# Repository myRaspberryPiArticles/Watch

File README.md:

# Watch
An analog IC chip watch powered with a LiPo and outputs in digital time on segment displays! Analog, or digital!? Thanks to Hackclub Forge and PCBWay for making this possible! Go check them out and make cool things like this as well! Here is more about it!:

## Pictures - _a picture tells 1000 words_
<p align="center">

</p>

## What does is it do? 
This watch is my V1 of a fully analog circuit, and by far the most complex PCB I have made. The aim is for it to be able to keep track of time precisely and then output it to four 7-segment displays, for the user to see when they have clicked the show time button. Usually, a watch would show the time constantly, but because  of battery constraints, I had to adapt to make it only show when the user wanted it to be seen. The 7-segment displays automatically wrap around after hitting 23:59, as it is the 24 hour clock's largest possible time. All the details will be explained in the 'How does it work' section.

## Why did I build it?
This specific project has a far fetched origin story, but the gist is that I wanted to do something with a 555 Timer after seeing a normal wristwatch, then comparing it with my smart watch, then thinking what is in the middle of the two - whether the thing I should make should be analog, or digital. 

After reasoning around with Gemini for a bit, I realised I would unfortunately have to use something closer to an oscillator rather than a 555 Timer as I hoped. In this chat, I also figured out how some of the other stuff would work, which brings us to our next section for those interested.

## How does it work? - _@techy people, this is for you_
The question we are all wondering. There is such a complex PCB and schematic we have seen in the photos, and now we at least know what it is - but how does it work? The simple answer can be broken into some few blocks and sections of the hardware, that eventually make the watch work. The blocks go as such:

1. Timer block (SG-3030CM gives a 32.768kHz pulse, then a 2^14 divider gets it down to 2Hz, then another divider to 1Hz) ---> 

2. Second to minute pulse block (two carry counter ICs that make the pulse 1/16Hz to input over to the display) ---> 

3. Display block (CD4026s that output to super small 0.2" segment displays) ---> 

4. And-gate wrap around (74HC08 IC that supplies quad 2 input and-gates for detecting certain segments)

## PCB and layout - _There is no greater optimism than ordering 500 boards without testing the prototype first._
As seen in the picture, the PCB is quite busy, with their being 701 trace segments, 258 pads, 73 vias, and a total of 123 nets. All these components have to fit in a wristwatch size of 35x42mm, and there are over 30 resistors and capacitors. To fit them all with enough space for a copper zone to pour, and to fit traces, I had to move over some parts to the back, but this means I will have to get a more advanced way of manufacturing it.

The way I was able to do this, with not much KiCAD experience was by logically splitting up the components, and wiring them one by one. this means I first made a display block with all the appropriate IC chips and resistors. After wiring them as needed, I then moved the m to a central position in the board to ensure there was enough space for the other components. then I fit in thew other timer units around where they could be inserted, before tracing them as well and then adding zones. I have two zones, on the back and front, for power and ground, and this meant I had to use many vias. To remove some random, useless copper zone islands, I had to use the 'do not fill' tool.

If you want a more chronological timeline of how I built this, check out my JOURNAL.md above!

## BOM - _NOT A BOMB!_
| Part | Where to buy | Cost |
| :--- | :---: | ---: |
| Segment Displays | [Ebay](https://www.ebay.co.uk/itm/195889276369?_skw=0.2%22+segment+display&itmmeta=01M6EP70M7ABXRD5BKFYGM1NHH&hash=item2d9be925d1%3Ag%3ATBIAAOSw2qplWLlX&itmprp=enc%3AAQALAAAA0CHNgUiiE%2FjQhlDTaMiAde8N4pqQcRs8IX6DydODM23mOmGth8nYc7n8xlrxr%2BS6NNEPMCjCPPxBPjypG0T%2B5PGzBhXTQX7kgbtBIbUk7yeaSZlJJ6amFuhsQ36oQ9b2yuffzb50OcMxg3q4ecM1aXkWZo%2F783288050KDa2ArMurpdlvRwuIxSIHRjXkyeuZAuIBqRyUxFpR0BJJzrU7XKouGydvSz2MxBBIo4o8Zub2EHKCbsUPWCddHyWID6wkAjNf4vrKmJSyS3vcDLDhIs%3D%7Ctkp%3ABk9SR7aKnNazaA&var=495722409176) | £6.00 |
| LiPo battery | [Amazon](https://www.amazon.co.uk/battery-200mAh-Lithium-Polymer-connection/dp/B0D7VSYPPV/ref=sr_1_1?crid=29NVIJLAAEKU9&dib=eyJ2IjoiMSJ9.X7pX1xi7ILp_yplrh-ou4Vn7LX2L5z4TSvIyitPoWCRTs833GjyNv_btAHxWWRVfidY4wBOOqi-bF9z36nFckCWh6gMjnExoc1Siyj5zNpM01Gdy7AxC1Yx6yceXOyPuezl3_dylYWErBcJeXORGgf_EmMsIkefHAp5C3YBVZepQy78KDg_m93ImNwE2-U-9F_XQ-JeKX3mFoFbwaYuhXktrl7TpZVMo1aGalGdQDR4.xiXYNVCcjwKY2whsgjaTlGsp_9Z_KdIO1XLzM3AwIMA&dib_tag=se&keywords=lipo%2Bbattery%2B3.7v%2Bsmall%2B200mAh&qid=1795460422&sprefix=lipo%2Bbattery%2B3.7v%2Bsmall%2B200mah%2Caps%2C161&sr=8-1&th=1) | £6.99 |
| Button | [AliExpress](https://www.aliexpress.com/item/1005012840797368.html?spm=a2g0o.productlist.main.5.443a124ch89hrB&algo_pvid=1b1f1828-bc73-4d8e-ac3d-791ba3cc20e5&algo_exp_id=1b1f1828-bc73-4d8e-ac3d-791ba3cc20e5-4&pdp_ext_f=%7B%22order%22%3A%225%22%2C%22eval%22%3A%221%22%2C%22fromPage%22%3A%22search%22%7D&pdp_npi=6%40dis%21GBP%212.21%212.07%21%21%212.81%212.63%21%400b0fe08917954597643931705e0eb7%2112000059495813788%21sea%21UK%216074049085%21X%211%210%21n_tag%3A-29919%3Bd%3A1f3ba004%3Bm03_new_user%3A-29895&curPageLogUid=LAaXCNjWhGwG&utparam-url=scene%3Asearch%7Cquery_from%3A%7Cx_object_id%3A1005012840797368%7C_p_origin_prod%3A) | ￡2.07 |
| JST port | [AliExpress](https://www.aliexpress.com/item/1005012356614470.html?spm=a2g0o.productlist.main.25.1ce37d798pSBfy&algo_pvid=5d2b104a-103d-42cd-820e-ac5102c88d9c&algo_exp_id=5d2b104a-103d-42cd-820e-ac5102c88d9c-24&pdp_ext_f=%7B%22order%22%3A%2265%22%2C%22eval%22%3A%221%22%2C%22fromPage%22%3A%22search%22%7D&pdp_npi=6%40dis%21GBP%211.31%211.21%21%21%2111.12%2110.23%21%400b5e1a3817954605730502025e0f96%2112000058175092939%21sea%21UK%216074049085%21X%211%210%21n_tag%3A-29919%3Bd%3A1f3ba004%3Bm03_new_user%3A-29895&curPageLogUid=Xan4gW2oVw1H&utparam-url=scene%3Asearch%7Cquery_from%3A%7Cx_object_id%3A1005012356614470%7C_p_origin_prod%3A) | ￡1.21 |

## Reviewer's note - _Bold of me to read the footnotes before understanding the title_
For the funding of this project, I have reached out to PCB way for there kind sponsorship programme, so the only parts that will need to be funded by Hackclub are the battery, button, case? (maybe), and finally the displays themselves.

Thank you to Hackclub Forge for helping bring this project to life!

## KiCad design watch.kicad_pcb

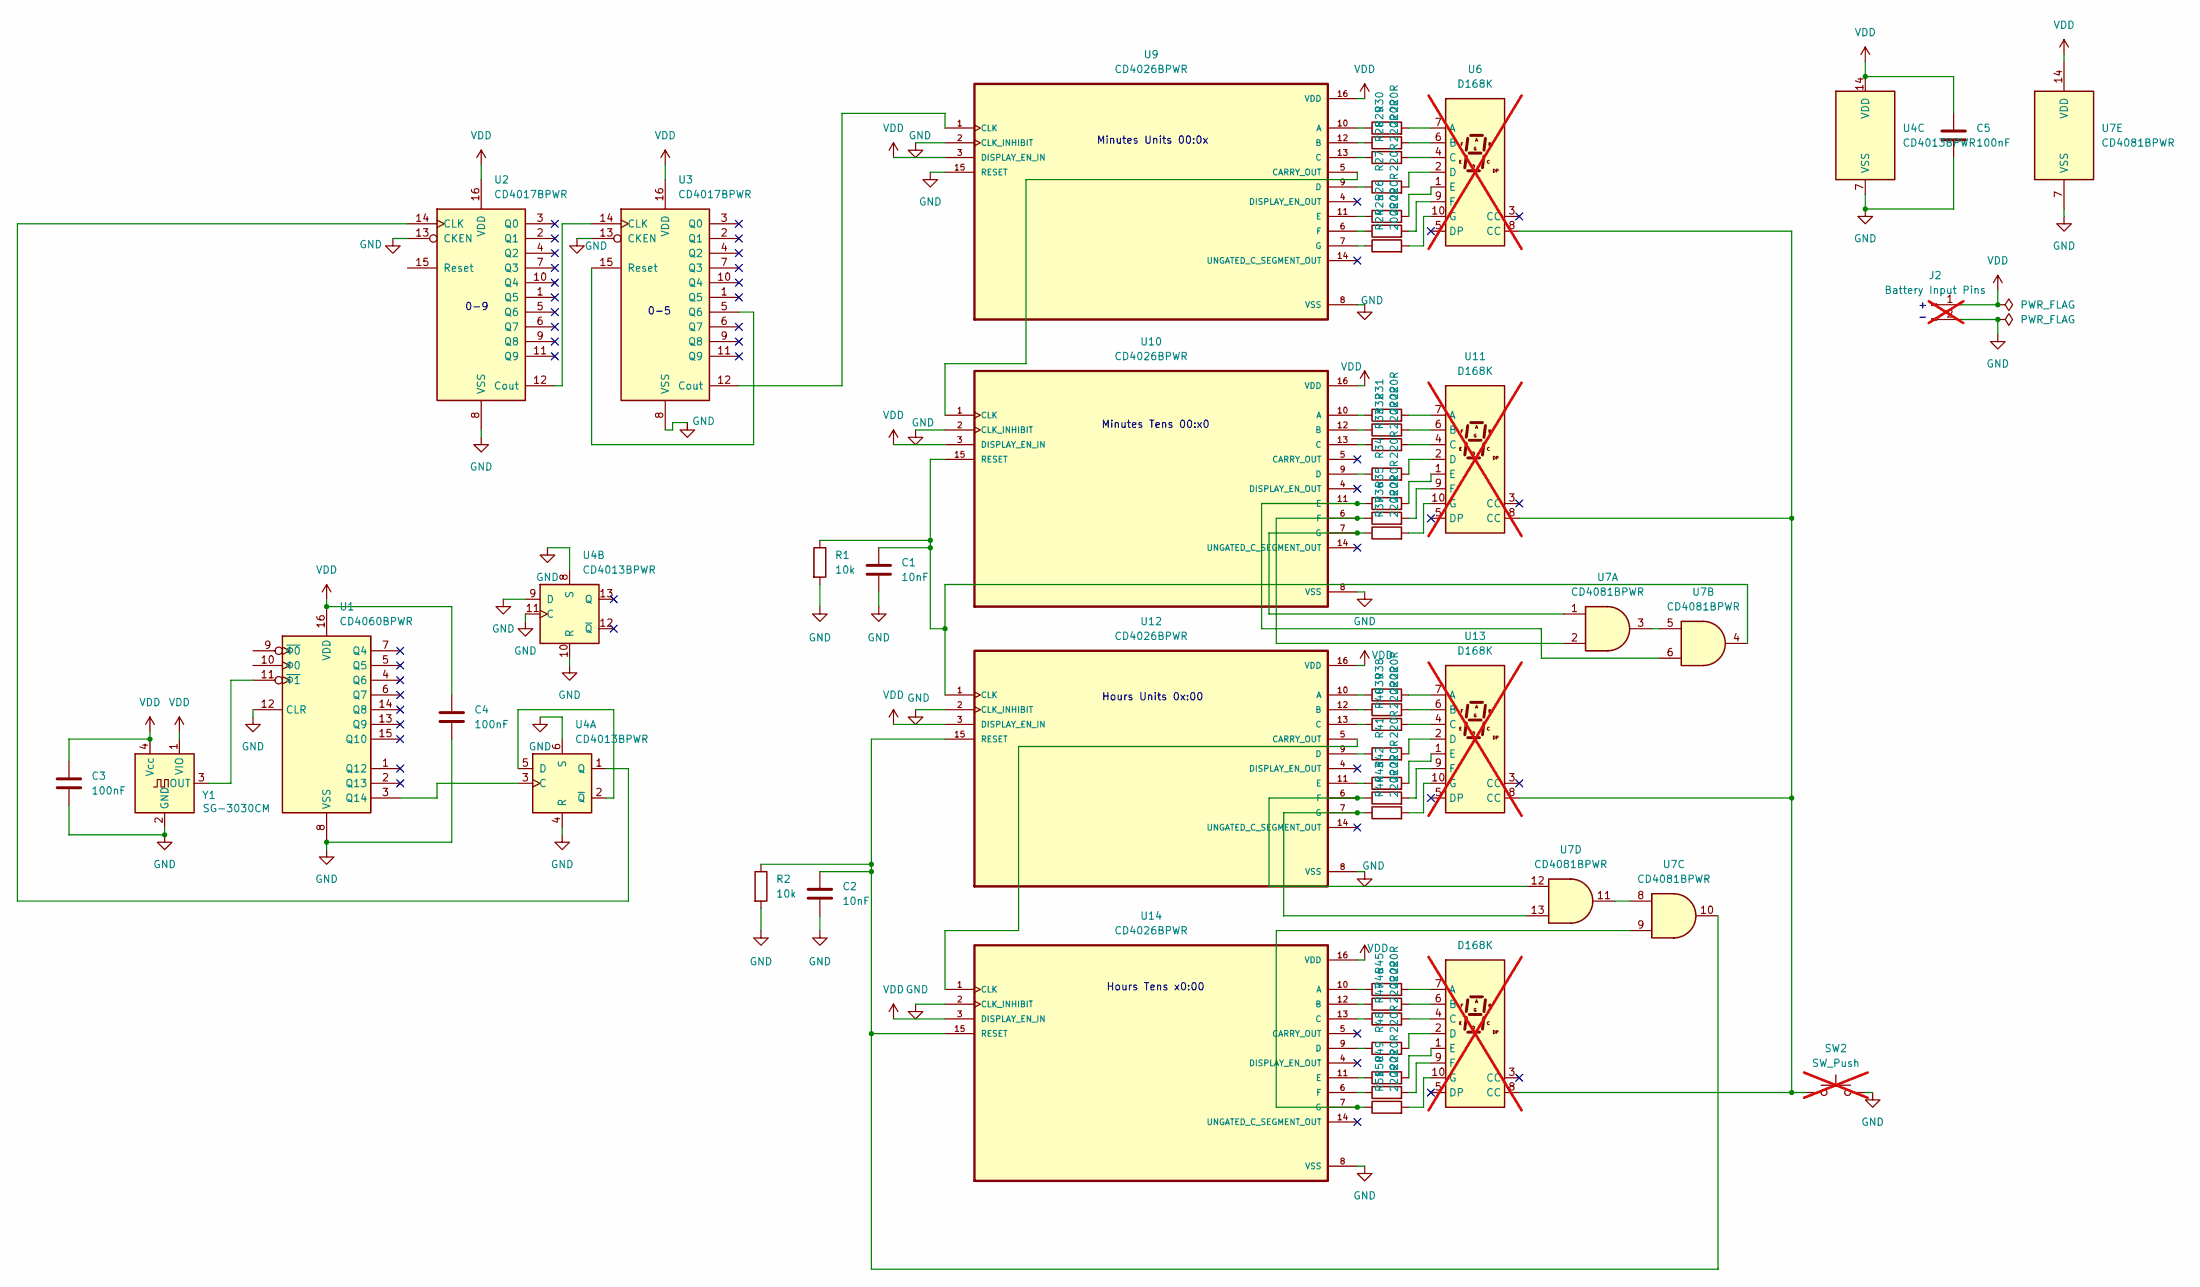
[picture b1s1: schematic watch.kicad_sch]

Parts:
C1, C2: 10nF; C_0603_1608Metric_Pad1.08x0.95mm_HandSolder
C3, C4, C5: 100nF; C_0603_1608Metric_Pad1.08x0.95mm_HandSolder
J2: Battery Input Pins; JST_PH_B2B-PH-K_1x02_P2.00mm_Vertical; not fitted
R1, R2: 10k; R_0603_1608Metric_Pad0.98x0.95mm_HandSolder
R24: 200R; R_0603_1608Metric_Pad0.98x0.95mm_HandSolder
R25, R26, R27, R28, R29, R30, R31, R32, R33, R34, R35, R36, R37, R38, R39, R40, R41, R42, R43, R44, R45, R46, R47, R48, R49, R50, R51: 220R; R_0603_1608Metric_Pad0.98x0.95mm_HandSolder
SW2: SW_Push; SW_PUSH_1P1T_6x3.5mm_H5.0_APEM_MJTP1250; not fitted
U1: CD4060BPWR; TSSOP-16_4.4x5mm_P0.65mm
U2, U3: CD4017BPWR; TSSOP-16_4.4x5mm_P0.65mm
U4: CD4013BPWR; TSSOP-14_4.4x5mm_P0.65mm
U6, U11, U13, U15: D168K; KCSC02-105; not fitted
U7: CD4081BPWR; TSSOP-14_4.4x5mm_P0.65mm
U9, U10, U12, U14: CD4026BPWR; TSSOP-16_4.4x5mm_P0.65mm
Y1: SG-3030CM; Oscillator_SMD_SeikoEpson_SG3030CM

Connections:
GND: C1.2, C2.2, C3.1, C4.2, C5.2, J2.2, R1.2, R2.2, SW2.2, U1.8 (VSS), U1.12 (CLR), U2.8 (VSS), U2.13 (CKEN), U3.8 (VSS), U3.13 (CKEN), U4.4 (R), U4.6 (S), U4.7 (VSS), U4.8 (S), U4.9 (D), U4.10 (R), U4.11 (C), U7.7 (VSS), U9.2 (CLK_INHIBIT), U9.8 (VSS), U9.15 (RESET), U10.2 (CLK_INHIBIT), U10.8 (VSS), U12.2 (CLK_INHIBIT), U12.8 (VSS), U14.2 (CLK_INHIBIT), U14.8 (VSS), Y1.2 (GND)
unnamed: SW2.1, U6.8 (CC), U11.8 (CC), U13.8 (CC), U15.8 (CC)
unnamed: U1.3 (Q14), U4.3 (C)
unnamed: U1.11 (~Φ1), Y1.3 (OUT)
unnamed: U2.14 (CLK), U4.1 (Q)
unnamed: U2.12 (Cout), U3.14 (CLK)
unnamed: U3.12 (Cout), U9.1 (CLK)
unnamed: U3.5 (Q6), U3.15 (Reset)
unnamed: U4.2 (~Q), U4.5 (D)
unnamed: R30.2, U6.7 (A)
unnamed: R29.2, U6.6 (B)
unnamed: R28.2, U6.4 (C)
unnamed: R27.2, U6.2 (D)
unnamed: R26.2, U6.1 (E)
unnamed: R25.2, U6.9 (F)
unnamed: R24.2, U6.10 (G)
unnamed: U7.3, U7.5
unnamed: U7.8, U7.11
unnamed: R30.1, U9.10 (A)
unnamed: R29.1, U9.12 (B)
unnamed: R28.1, U9.13 (C)
unnamed: R27.1, U9.9 (D)
unnamed: R26.1, U9.11 (E)
unnamed: R25.1, U9.6 (F)
unnamed: R24.1, U9.7 (G)
unnamed: R31.1, U10.10 (A)
unnamed: R32.1, U10.12 (B)
unnamed: R33.1, U10.13 (C)
unnamed: U9.5 (CARRY_OUT), U10.1 (CLK)
unnamed: R34.1, U10.9 (D)
unnamed: R35.1, U7.6, U10.11 (E)
unnamed: R36.1, U7.2, U10.6 (F)
unnamed: R37.1, U7.1, U10.7 (G)
unnamed: C1.1, R1.1, U7.4, U10.15 (RESET), U12.1 (CLK)
unnamed: R31.2, U11.7 (A)
unnamed: R32.2, U11.6 (B)
unnamed: R33.2, U11.4 (C)
unnamed: R34.2, U11.2 (D)
unnamed: R35.2, U11.1 (E)
unnamed: R36.2, U11.9 (F)
unnamed: R37.2, U11.10 (G)
unnamed: R38.1, U12.10 (A)
unnamed: R39.1, U12.12 (B)
unnamed: R40.1, U12.13 (C)
unnamed: U12.5 (CARRY_OUT), U14.1 (CLK)
unnamed: R41.1, U12.9 (D)
unnamed: R42.1, U12.11 (E)
unnamed: R43.1, U7.12, U12.6 (F)
unnamed: R44.1, U7.13, U12.7 (G)
unnamed: C2.1, R2.1, U7.10, U12.15 (RESET), U14.15 (RESET)
unnamed: R38.2, U13.7 (A)
unnamed: R39.2, U13.6 (B)
unnamed: R40.2, U13.4 (C)
unnamed: R41.2, U13.2 (D)
unnamed: R42.2, U13.1 (E)
unnamed: R43.2, U13.9 (F)
unnamed: R44.2, U13.10 (G)
unnamed: R45.1, U14.10 (A)
unnamed: R46.1, U14.12 (B)
unnamed: R47.1, U14.13 (C)
unnamed: R48.1, U14.9 (D)
unnamed: R49.1, U14.11 (E)
unnamed: R50.1, U14.6 (F)
unnamed: R51.1, U7.9, U14.7 (G)
unnamed: R45.2, U15.7 (A)
unnamed: R46.2, U15.6 (B)
unnamed: R47.2, U15.4 (C)
unnamed: R48.2, U15.2 (D)
unnamed: R49.2, U15.1 (E)
unnamed: R50.2, U15.9 (F)
unnamed: R51.2, U15.10 (G)
VDD: C3.2, C4.1, C5.1, J2.1, U1.16 (VDD), U2.16 (VDD), U3.16 (VDD), U4.14 (VDD), U7.14 (VDD), U9.3 (DISPLAY_EN_IN), U9.16 (VDD), U10.3 (DISPLAY_EN_IN), U10.16 (VDD), U12.3 (DISPLAY_EN_IN), U12.16 (VDD), U14.3 (DISPLAY_EN_IN), U14.16 (VDD), Y1.1 (VIO), Y1.4 (Vcc)

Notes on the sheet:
Minutes Units 00:0x
Hours Units 0x:00
+ -
Minutes Tens 00:x0
0-5
Hours Tens x0:00
0-9

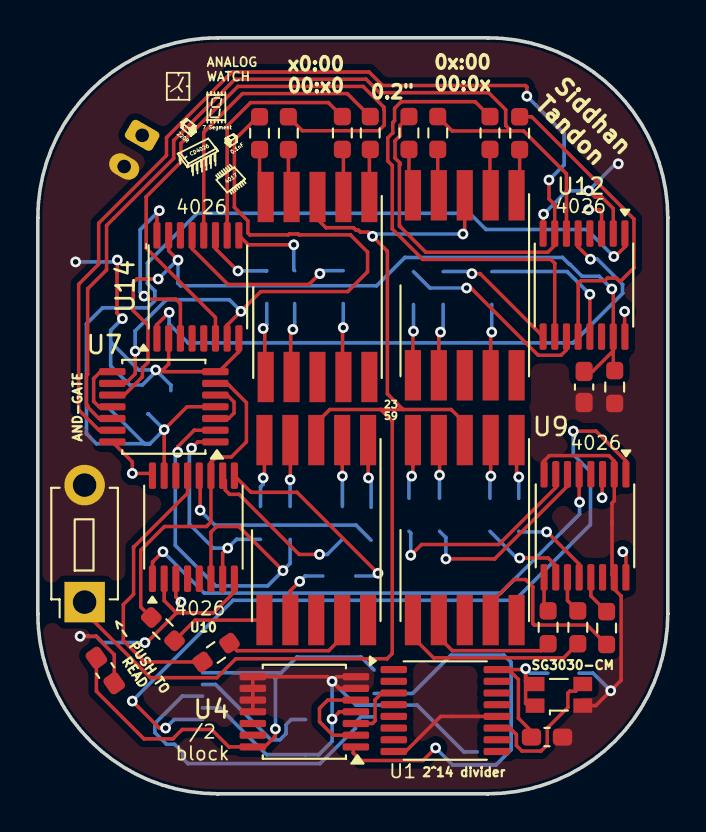
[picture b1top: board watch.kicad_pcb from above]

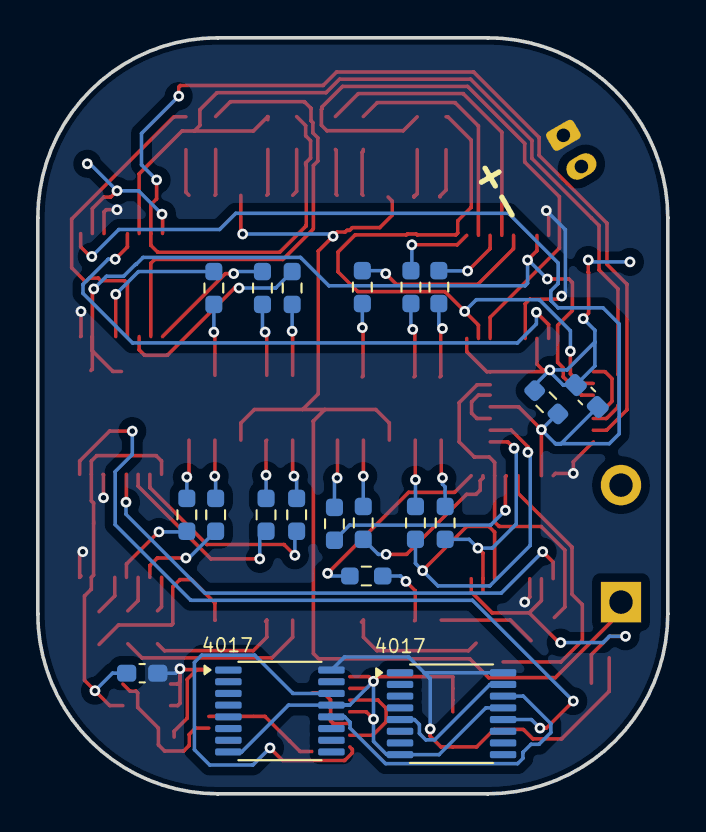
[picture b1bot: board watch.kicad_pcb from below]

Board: 2 copper layers, 35.0 x 42.0 mm, 51 parts (21 on the bottom side), 72 nets.
